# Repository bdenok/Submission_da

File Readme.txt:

Student Name: Brayden Okubo

Student #: 2002230890

Student Email: OKubob1@unlv.nevada.edu

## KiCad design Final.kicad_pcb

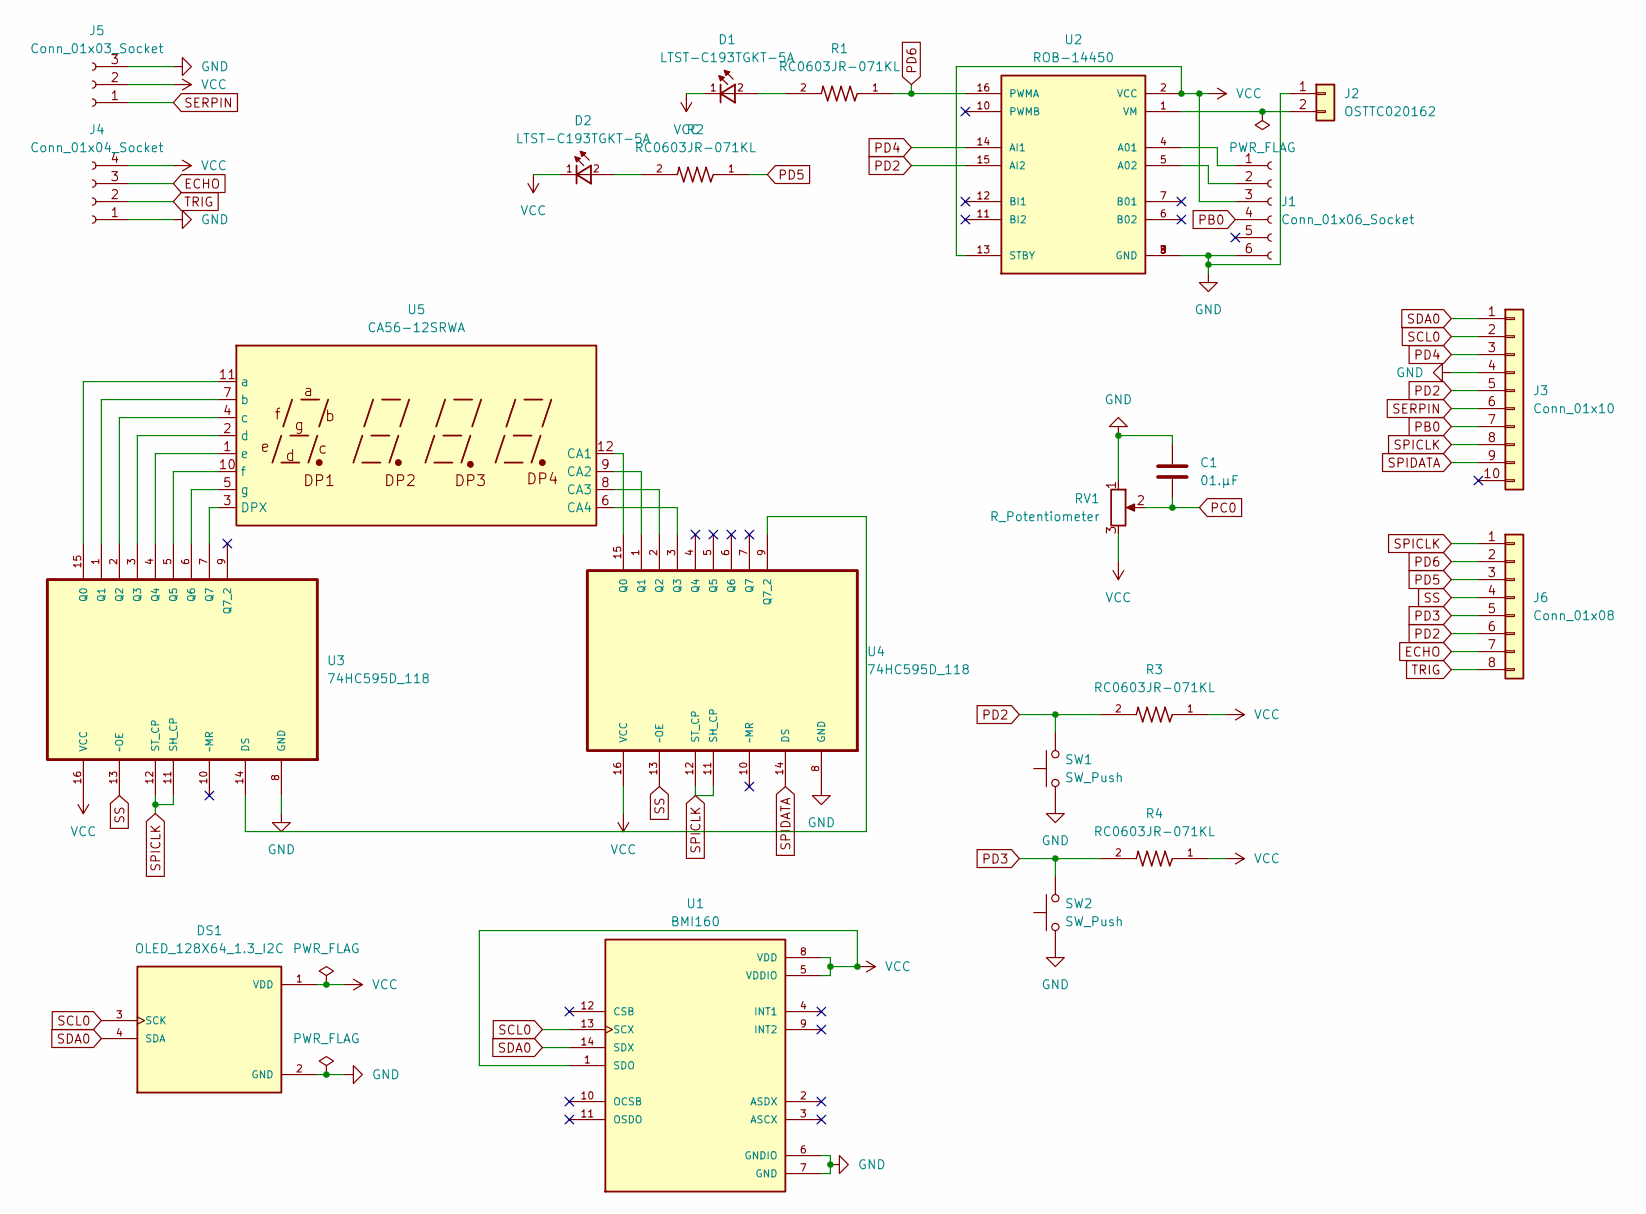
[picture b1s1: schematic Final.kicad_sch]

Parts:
C1: 01.µF; C_0805_2012Metric
D1, D2: LTST-C193TGKT-5A; 0603
DS1: OLED_128X64_1.3_I2C; LCD_OLED_128X64_1.3_I2C; PARTREV NA
J1: Conn_01x06_Socket; PinHeader_1x06_P2.54mm_Vertical
J2: OSTTC020162; JST_XH_B2B-XH-A_1x02_P2.50mm_Vertical
J3: Conn_01x10; PinHeader_1x10_P2.54mm_Vertical
J4: Conn_01x04_Socket; PinHeader_1x04_P2.54mm_Vertical
J5: Conn_01x03_Socket; PinHeader_1x03_P2.54mm_Vertical
J6: Conn_01x08; PinHeader_1x08_P2.54mm_Vertical
R1, R2, R3, R4: RC0603JR-071KL; RESC1607X60N
RV1: R_Potentiometer; Potentiometer_Bourns_3339H_Vertical
SW1, SW2: SW_Push; SW_PUSH_6mm
U1: BMI160; PQFN50P250X300X88-14N; PARTREV 1.0
U2: ROB-14450; MODULE_ROB-14450; PARTREV 11-13-17
U3, U4: 74HC595D_118; SOIC127P600X175-16N; MPN 74HC595D,118
U5: CA56-12SRWA

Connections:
ECHO: J4.3, J6.7
GND: C1.1, DS1.2 (GND), J1.6, J2.1, J3.4, J4.1, J5.3, RV1.1, SW1.1, SW2.1, U1.6 (GNDIO), U1.7 (GND), U2.3 (GND), U2.8 (GND), U2.9 (GND), U3.8 (GND), U4.8 (GND)
unnamed: D1.2, R1.2
unnamed: D2.2, R2.2
unnamed: J1.1, U2.4 (A01)
unnamed: J1.2, U2.5 (A02)
unnamed: J2.2, U2.1 (VM)
unnamed: U3.14 (DS), U4.9 (Q7_2)
unnamed: U3.15 (Q0), U5.11 (a)
unnamed: U3.1 (Q1), U5.7 (b)
unnamed: U3.2 (Q2), U5.4 (c)
unnamed: U3.3 (Q3), U5.2 (d)
unnamed: U3.4 (Q4), U5.1 (e)
unnamed: U3.5 (Q5), U5.10 (f)
unnamed: U3.6 (Q6), U5.5 (g)
unnamed: U3.7 (Q7), U5.3 (DPX)
unnamed: U4.15 (Q0), U5.12 (CA1)
unnamed: U4.1 (Q1), U5.9 (CA2)
unnamed: U4.2 (Q2), U5.8 (CA3)
unnamed: U4.3 (Q3), U5.6 (CA4)
PB0: J1.4, J3.7
PC0: C1.2, RV1.2
PD2: J3.5, J6.6, R3.2, SW1.2, U2.15 (AI2)
PD3: J6.5, R4.2, SW2.2
PD4: J3.3, U2.14 (AI1)
PD5: J6.3, R2.1
PD6: J6.2, R1.1, U2.16 (PWMA)
SCL0: DS1.3 (SCK), J3.2, U1.13 (SCX)
SDA0: DS1.4 (SDA), J3.1, U1.14 (SDX)
SERPIN: J3.6, J5.1
SPICLK: J3.8, J6.1, U3.11 (SH_CP), U3.12 (ST_CP), U4.11 (SH_CP), U4.12 (ST_CP)
SPIDATA: J3.9, U4.14 (DS)
SS: J6.4, U3.13 (~OE), U4.13 (~OE)
TRIG: J4.2, J6.8
VCC: D1.1, D2.1, DS1.1 (VDD), J1.3, J4.4, J5.2, R3.1, R4.1, RV1.3, U1.1 (SDO), U1.5 (VDDIO), U1.8 (VDD), U2.2 (VCC), U2.13 (STBY), U3.16 (VCC), U4.16 (VCC)

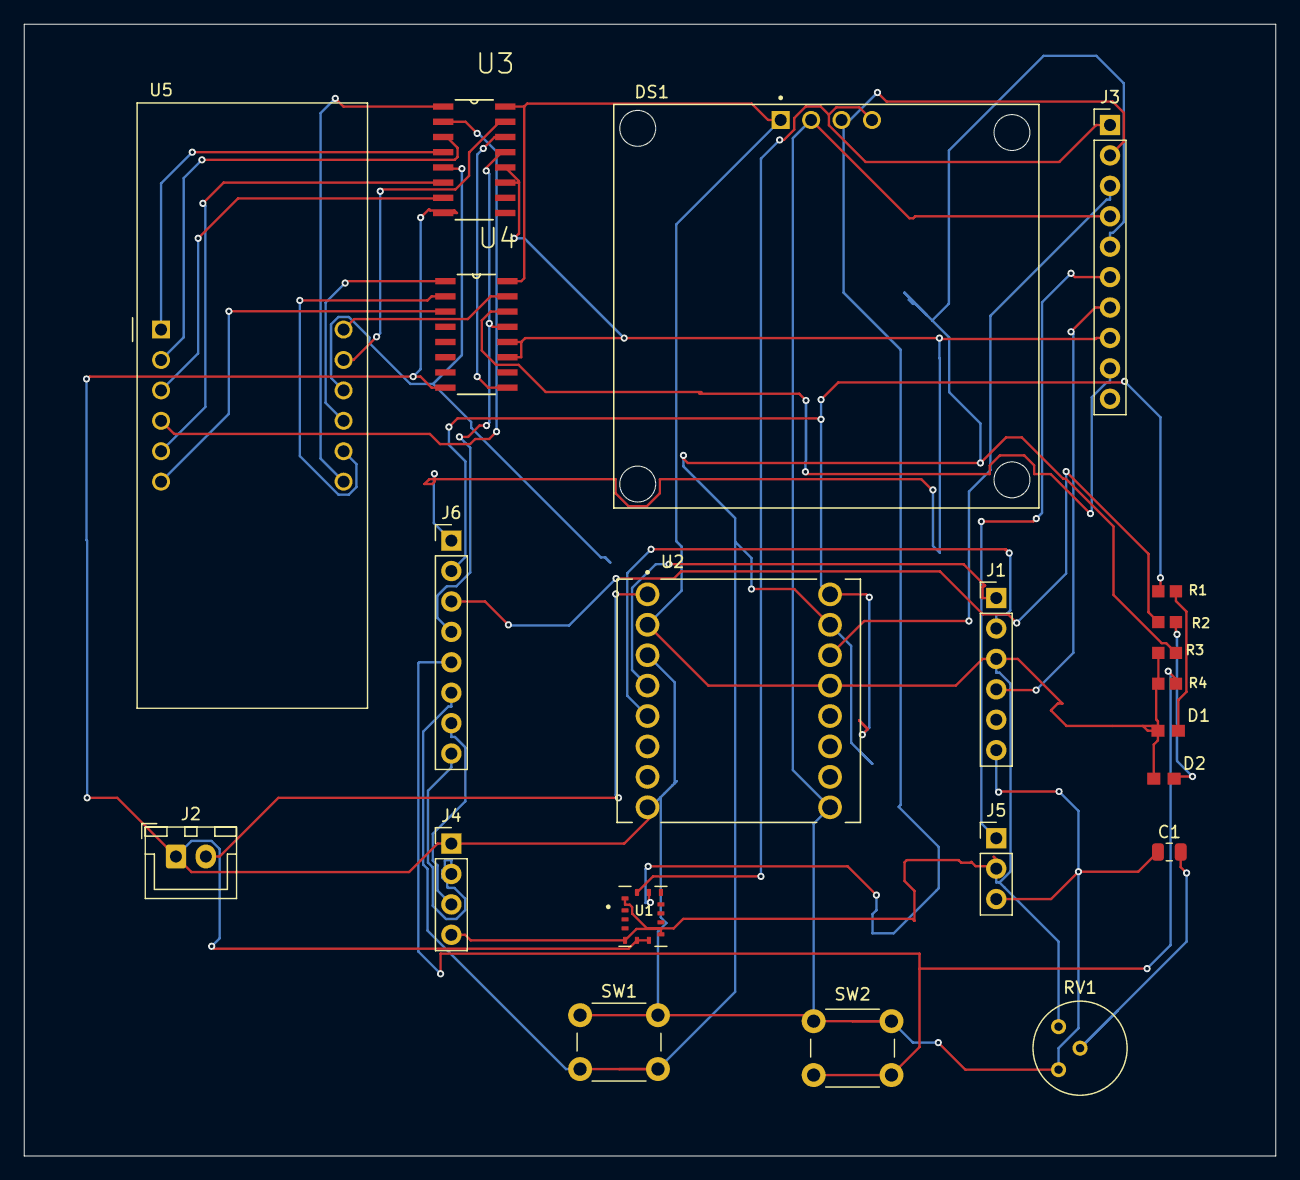
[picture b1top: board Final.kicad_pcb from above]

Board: 2 copper layers, 104.5 x 94.5 mm, 22 parts (0 on the bottom side), 35 nets.

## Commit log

2025-03-29 Create CPE301 DA3
